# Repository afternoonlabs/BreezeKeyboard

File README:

# Breeze

> Ergonomics meets Productivity.

## Introduction

"Breeze" is a split mechanical keyboard with a column-staggered layout. With a focus on productivity, Breeze features a full 6x4 alphanumeric layout, arrow keys, and an extra 6 key cluster for typing and coding.

Learn more at: [www.afternoonlabs.com](https://www.afternoonlabs.com)

## Features

* Split Ergonomics
* Productivity Cluster for Typing and Coding
* Open-source PCB design for easy modifications
* Hotswap MX or Choc Sockets
* Option to Manufacture with Diodes Built-in, No Diode Soldering Required
* Columnar Stagger
* Arrow Keys!
* QMK, Pro Micro, VIA Compatible
* Bonus 6 Key or 9 Key Macro Pad Included (The **Gust** Macro Pad)

## License

Anyone can use this for any purpose. Distributed under the MIT License. See `LICENSE` for more information.

My only request is that if someone uses this design to create new keyboard, I'd like to try it :).

## Getting Started

These instructions will guide you on how to replicate this keyboard design on your local machine for development, testing, or personal use.

For instructions for assembly of a Breeze keyboard once you have a PCB, follow [the official build guide](https://www.afternoonlabs.com/breeze/build-guide).

### Prerequisites

Before starting, make sure you have:

* KiCad 6 or later installed
* Basic understanding of electronic circuit design
* Basic understanding of mechanical keyboard assembly

### Installation

Follow these steps to get a copy of the project up and running:

1. Clone the repository

```bash
git clone https://github.com/afternoonlabs/BreezeKeyboard
```

2. Open the project `Breeze.kicad_pro` file with KiCad

3. Now, you can view, edit, and export the schematic and PCB layout for manufacturing.

## Contribution

Contributions are encouraged! Whether it's bug fixes, new features, or even simple feedback, everything helps in making the project better.

1. Fork the Project
2. Create your Feature Branch (`git checkout -b feature/SomeFeature`)
3. Commit your Changes (`git commit -m 'Adding SomeFeature'`)
4. Push to the Branch (`git push origin feature/SomeFeature`)
5. Open a Pull Request

## Contact

Afternoon Labs - [hi@afternoonlabs.com](mailto:hi@afternoonlabs.com)

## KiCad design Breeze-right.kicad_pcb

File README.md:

# Breeze

> Ergonomics meets Productivity.

## Introduction

"Breeze" is a split mechanical keyboard with a column-staggered layout. With a focus on productivity, Breeze features a full 6x4 alphanumeric layout, arrow keys, and an extra 6 key cluster for typing and coding.

Learn more at: [www.afternoonlabs.com](https://www.afternoonlabs.com)

## Features

* Split Ergonomics
* Productivity Cluster for Typing and Coding
* Open-source PCB design for easy modifications
* Hotswap MX or Choc Sockets
* Option to Manufacture with Diodes Built-in, No Diode Soldering Required
* Columnar Stagger
* Arrow Keys!
* QMK, Pro Micro, VIA Compatible
* Bonus 6 Key or 9 Key Macro Pad Included (The **Gust** Macro Pad)

## Getting Started

These instructions will guide you on how to replicate this keyboard design on your local machine for development, testing, or personal use.

For instructions for assembly of a Breeze keyboard once you have a PCB, follow [the official build guide](https://www.afternoonlabs.com/breeze/build-guide).

### Prerequisites

Before starting, make sure you have:

* KiCad 6 or later installed
* Basic understanding of electronic circuit design
* Basic understanding of mechanical keyboard assembly

### Installation

Follow these steps to get a copy of the project up and running:

1. Clone the repository

```bash
git clone https://github.com/afternoonlabs/BreezeKeyboard
```

2. Open the project `Breeze.kicad_pro` file with KiCad

3. Now, you can view, edit, and export the schematic and PCB layout for manufacturing.

## Support us

Enjoying the Breeze? [Buy me a beer](https://www.buymeacoffee.com/Afternoonlabs).

## Contribution

Contributions are encouraged! Whether it's bug fixes, new features, or even simple feedback, everything helps in making the project better.

1. Fork the Project
2. Create your Feature Branch (`git checkout -b feature/SomeFeature`)
3. Commit your Changes (`git commit -m 'Adding SomeFeature'`)
4. Push to the Branch (`git push origin feature/SomeFeature`)
5. Open a Pull Request

## License

Anyone can use this project for personal use. Distributed under the MIT License. See `LICENSE` for more information.

Vendors interested in selling the Breeze, please contact us below.

The use of "Afternoon Labs" is protected under copyright law. Unauthorized use without express permission from "Afternoon Labs", is prohibited.

## Contact

Join our [Discord Server](https://discord.gg/9nsApe3GvG).

Afternoon Labs - [hi@afternoonlabs.com](mailto:hi@afternoonlabs.com)

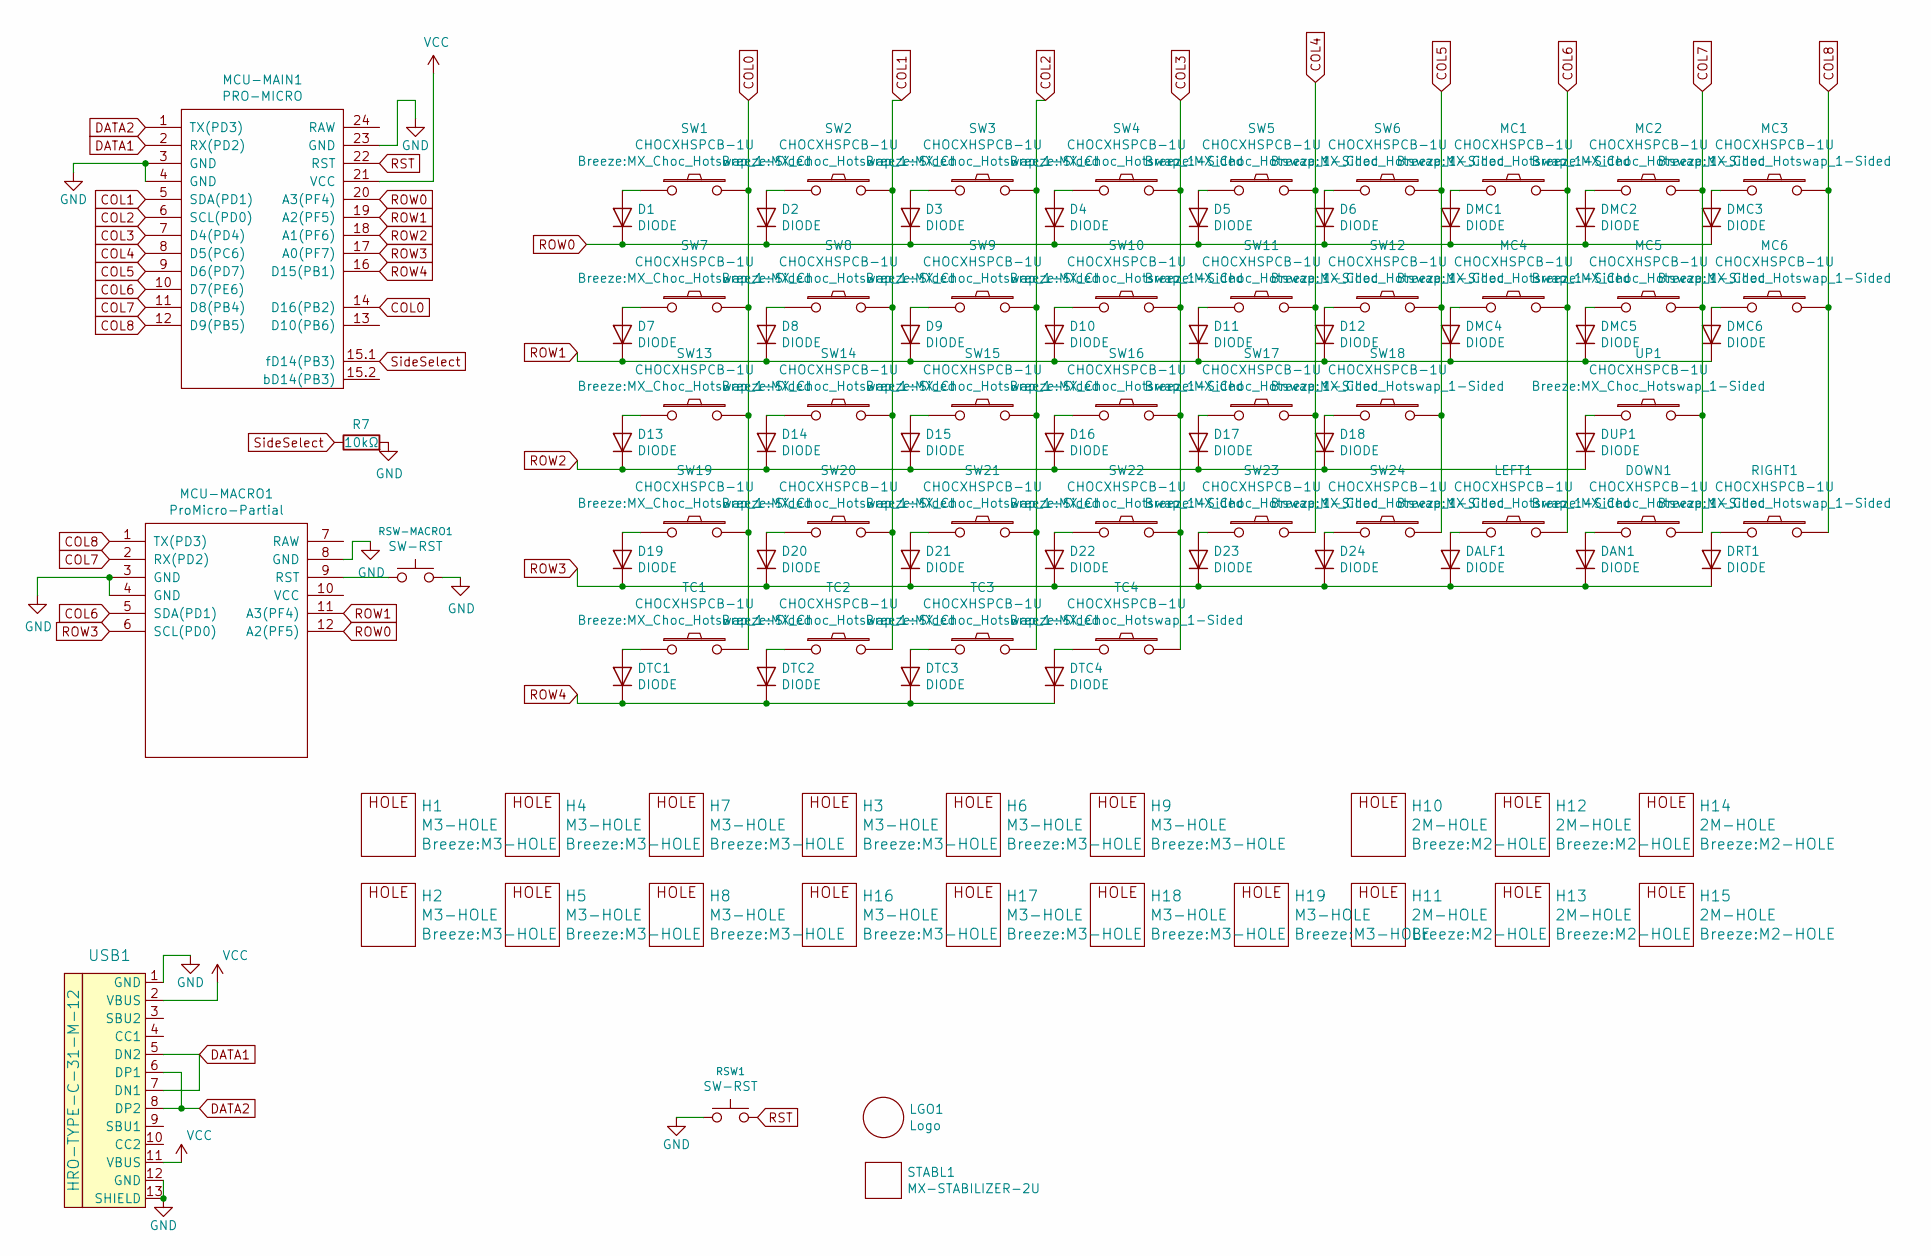
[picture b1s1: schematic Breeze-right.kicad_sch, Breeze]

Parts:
D1, D2, D3, D4, D5, D6, D7, D8, D9, D10, D11, D12, D13, D14, D15, D16, D17, D18, D19, D20, D21, D22, D23, D24: DIODE; SOD-123FL; LCSC C64898
DALF1: DIODE; SOD-123FL; LCSC C64898
DAN1: DIODE; SOD-123FL; LCSC C64898
DMC1, DMC2, DMC3, DMC4, DMC5, DMC6: DIODE; SOD-123FL; LCSC C64898
DOWN1: CHOCXHSPCB-1U; MX_Choc_Hotswap_1-Sided
DRT1: DIODE; SOD-123FL; LCSC C64898
DTC1, DTC2, DTC3, DTC4: DIODE; SOD-123FL; LCSC C64898
DUP1: DIODE; SOD-123FL; LCSC C64898
H1, H2, H3, H4, H5, H6, H7, H8, H9, H16, H17, H18, H19: M3-HOLE
H10, H11, H12, H13, H14, H15: 2M-HOLE; M2-HOLE
LEFT1: CHOCXHSPCB-1U; MX_Choc_Hotswap_1-Sided
LGO1: Logo; logo
MC1, MC2, MC3, MC4, MC5, MC6: CHOCXHSPCB-1U; MX_Choc_Hotswap_1-Sided
MCU-MACRO1: ProMicro-Partial; PROMICRO-PARTIAL2
MCU-MAIN1: PRO-MICRO; ProMicro_1-Sided
R7: 10kΩ; R_0603_1608Metric
RIGHT1: CHOCXHSPCB-1U; MX_Choc_Hotswap_1-Sided
RSW1: SW-RST; SW_SPST_TL3342
RSW-MACRO1: SW-RST; SW_SPST_TL3342
STABL1: MX-STABILIZER-2U; Stabilizer_MX_2u
SW1, SW2, SW3, SW4, SW5, SW6, SW7, SW8, SW9, SW10, SW11, SW12, SW13, SW14, SW15, SW16, SW17, SW18, SW19, SW20, SW21, SW22, SW23, SW24: CHOCXHSPCB-1U; MX_Choc_Hotswap_1-Sided
TC1, TC2, TC3, TC4: CHOCXHSPCB-1U; MX_Choc_Hotswap_1-Sided
UP1: CHOCXHSPCB-1U; MX_Choc_Hotswap_1-Sided
USB1: HRO-TYPE-C-31-M-12; USB-C-12-Pin-MidMount

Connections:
COL0: MCU-MAIN1.14 (D16(PB2)), SW1.2, SW7.2, SW13.2, SW19.2, TC1.2
COL1: MCU-MAIN1.5 (SDA(PD1)), SW2.2, SW8.2, SW14.2, SW20.2, TC2.2
COL2: MCU-MAIN1.6 (SCL(PD0)), SW3.2, SW9.2, SW15.2, SW21.2, TC3.2
COL3: MCU-MAIN1.7 (D4(PD4)), SW4.2, SW10.2, SW16.2, SW22.2, TC4.2
COL4: MCU-MAIN1.8 (D5(PC6)), SW5.2, SW11.2, SW17.2, SW23.2
COL5: MCU-MAIN1.9 (D6(PD7)), SW6.2, SW12.2, SW18.2, SW24.2
COL6: LEFT1.2, MC1.2, MC4.2, MCU-MACRO1.5 (SDA(PD1)), MCU-MAIN1.10 (D7(PE6))
COL7: DOWN1.2, MC2.2, MC5.2, MCU-MACRO1.2 (RX(PD2)), MCU-MAIN1.11 (D8(PB4)), UP1.2
COL8: MC3.2, MC6.2, MCU-MACRO1.1 (TX(PD3)), MCU-MAIN1.12 (D9(PB5)), RIGHT1.2
DATA1: MCU-MAIN1.2 (RX(PD2)), USB1.5 (DN2), USB1.7 (DN1)
DATA2: MCU-MAIN1.1 (TX(PD3)), USB1.6 (DP1), USB1.8 (DP2)
GND: MCU-MACRO1.3 (GND), MCU-MACRO1.4 (GND), MCU-MACRO1.8 (GND), MCU-MAIN1.3 (GND), MCU-MAIN1.4 (GND), MCU-MAIN1.23 (GND), RSW1.1, RSW-MACRO1.2, USB1.1 (GND), USB1.12 (GND), USB1.13 (SHIELD); also elsewhere on the board
unnamed: D1.2 (A), SW1.1
unnamed: D2.2 (A), SW2.1
unnamed: D3.2 (A), SW3.1
unnamed: D4.2 (A), SW4.1
unnamed: D5.2 (A), SW5.1
unnamed: D6.2 (A), SW6.1
unnamed: D7.2 (A), SW7.1
unnamed: D8.2 (A), SW8.1
unnamed: D9.2 (A), SW9.1
unnamed: D10.2 (A), SW10.1
unnamed: D11.2 (A), SW11.1
unnamed: D12.2 (A), SW12.1
unnamed: D13.2 (A), SW13.1
unnamed: D14.2 (A), SW14.1
unnamed: D15.2 (A), SW15.1
unnamed: D16.2 (A), SW16.1
unnamed: D17.2 (A), SW17.1
unnamed: D18.2 (A), SW18.1
unnamed: D19.2 (A), SW19.1
unnamed: D20.2 (A), SW20.1
unnamed: D21.2 (A), SW21.1
unnamed: D22.2 (A), SW22.1
unnamed: D23.2 (A), SW23.1
unnamed: D24.2 (A), SW24.1
unnamed: DALF1.2 (A), LEFT1.1
unnamed: DAN1.2 (A), DOWN1.1
unnamed: DMC1.2 (A), MC1.1
unnamed: DMC2.2 (A), MC2.1
unnamed: DMC3.2 (A), MC3.1
unnamed: DMC4.2 (A), MC4.1
unnamed: DMC5.2 (A), MC5.1
unnamed: DMC6.2 (A), MC6.1
unnamed: DRT1.2 (A), RIGHT1.1
unnamed: DTC1.2 (A), TC1.1
unnamed: DTC2.2 (A), TC2.1
unnamed: DTC3.2 (A), TC3.1
unnamed: DTC4.2 (A), TC4.1
unnamed: DUP1.2 (A), UP1.1
unnamed: MCU-MACRO1.9 (RST), RSW-MACRO1.1
ROW0: D1.1 (K), D2.1 (K), D3.1 (K), D4.1 (K), D5.1 (K), D6.1 (K), DMC1.1 (K), DMC2.1 (K), DMC3.1 (K), MCU-MACRO1.12 (A2(PF5)), MCU-MAIN1.20 (A3(PF4))
ROW1: D7.1 (K), D8.1 (K), D9.1 (K), D10.1 (K), D11.1 (K), D12.1 (K), DMC4.1 (K), DMC5.1 (K), DMC6.1 (K), MCU-MACRO1.11 (A3(PF4)), MCU-MAIN1.19 (A2(PF5))
ROW2: D13.1 (K), D14.1 (K), D15.1 (K), D16.1 (K), D17.1 (K), D18.1 (K), DUP1.1 (K), MCU-MAIN1.18 (A1(PF6))
ROW3: D19.1 (K), D20.1 (K), D21.1 (K), D22.1 (K), D23.1 (K), D24.1 (K), DALF1.1 (K), DAN1.1 (K), DRT1.1 (K), MCU-MACRO1.6 (SCL(PD0)), MCU-MAIN1.17 (A0(PF7))
ROW4: DTC1.1 (K), DTC2.1 (K), DTC3.1 (K), DTC4.1 (K), MCU-MAIN1.16 (D15(PB1))
RST: MCU-MAIN1.22 (RST), RSW1.2
SideSelect: MCU-MAIN1.15.1 (fD14(PB3)); also elsewhere on the board
VCC: MCU-MAIN1.21 (VCC), USB1.2 (VBUS), USB1.11 (VBUS)

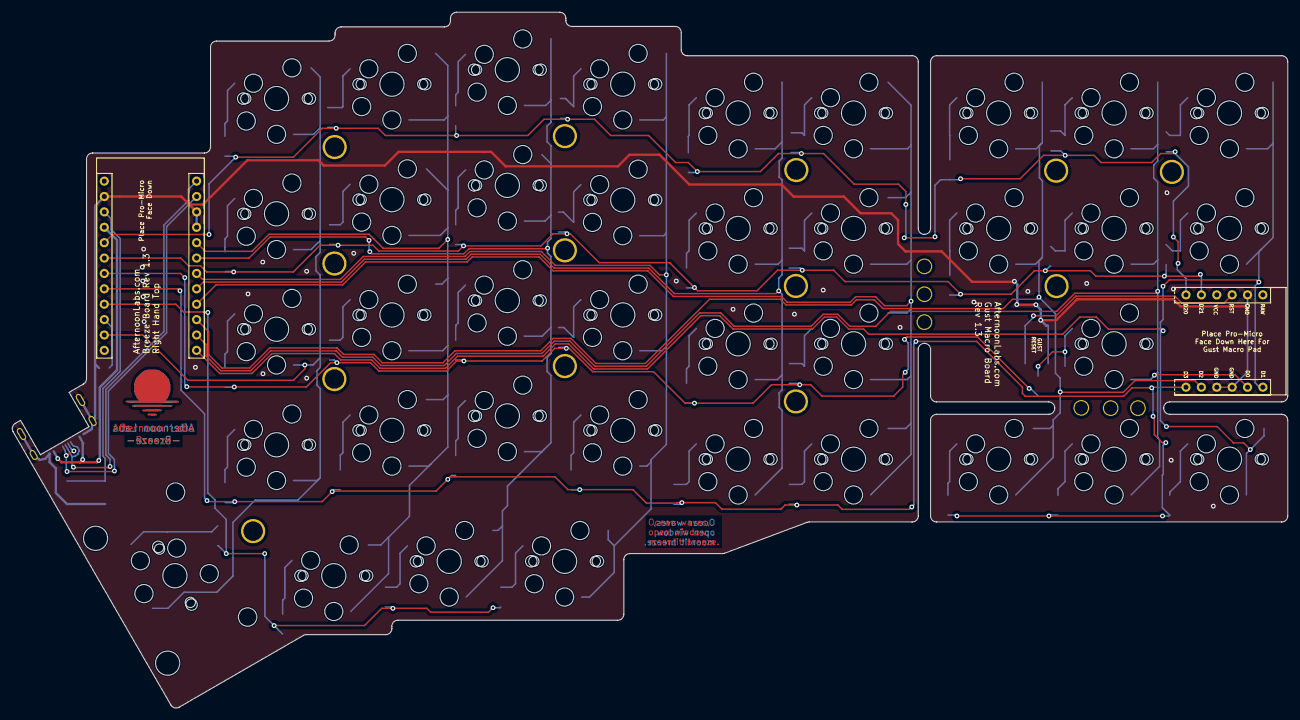
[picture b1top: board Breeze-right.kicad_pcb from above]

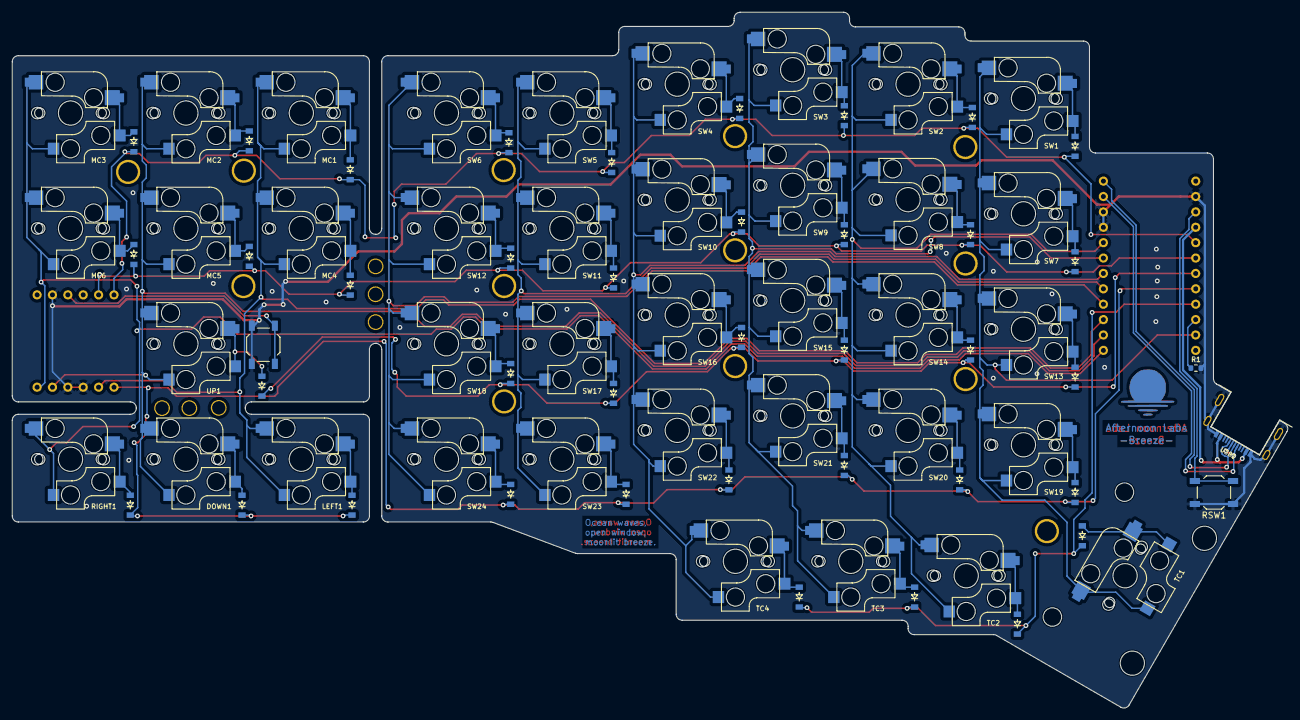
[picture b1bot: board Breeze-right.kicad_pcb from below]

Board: 2 copper layers, 210.6 x 114.9 mm, 103 parts (42 on the bottom side), 59 nets.

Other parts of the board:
R1: 10kΩ; R_0603_1608Metric

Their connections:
GND: R1.2; also elsewhere on the board
SideSelect: R1.1; also elsewhere on the board

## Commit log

2023-05-21 Open sourcing :)
2023-05-21 Rename README to README.md
2023-05-24 Adding Afternoon Labs logo to README.md
2023-05-24 Update README.md
    Update to legal text
2023-05-25 Adding a donation link
2023-05-25 Linking discord on README
2023-08-28 Update KiCAD format
2023-08-28 Switch interconnect TRRS to USB-C, change to SMD reset button (rerouting of traces not done)
2023-08-28 Fork design off into left and right halves
2023-08-29 Add 1-sided Pro Micro and socket footprints, add USB-C mid-mount, add 3D models
2023-08-29 Move diodes to bottom side, switch to single-sided Pro Micro and sockets
2023-08-29 Copy right half to left
2023-08-29 Set side select config for left half
2023-09-01 Remove stray line on silkscreen
2023-09-01 Remove extra holes and switches for breakoff portion on left half
2023-09-01 Route left hal
2023-09-01 Update switch footprint to fix silkscreen lines
